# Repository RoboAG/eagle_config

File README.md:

# eagle_config
basics for eagle
 + simple example (logic)
 + some handy shortcuts
 + library for robotics club

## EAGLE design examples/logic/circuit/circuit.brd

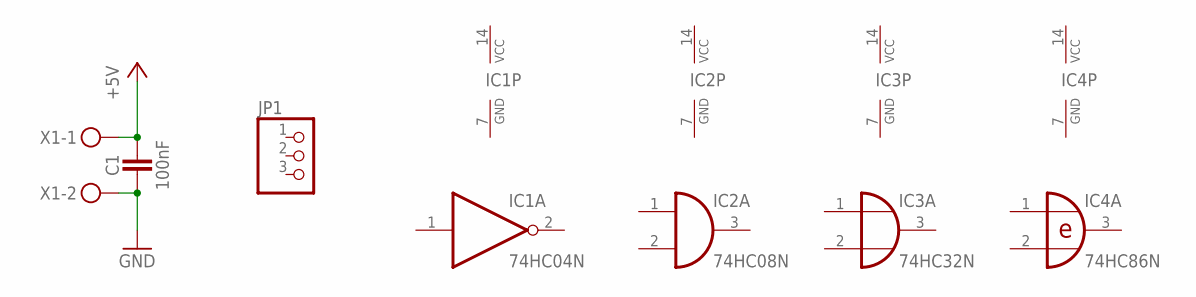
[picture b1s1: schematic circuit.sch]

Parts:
C1: 100nF; C_THT_3
IC1: 74HC04N; DIL14
IC2: 74HC08N; DIL14
IC3: 74HC32N; DIL14
IC4: 74HC86N; DIL14
JP1: PINHD-1X3; 1X03
X1: STECKER_SPG_2

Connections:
+5V: C1.1, X1.1
GND: C1.2, IC1.7 (GND), IC2.7 (GND), IC3.7 (GND), IC4.7 (GND), X1.2
VCC: IC1.14 (VCC), IC2.14 (VCC), IC3.14 (VCC), IC4.14 (VCC)

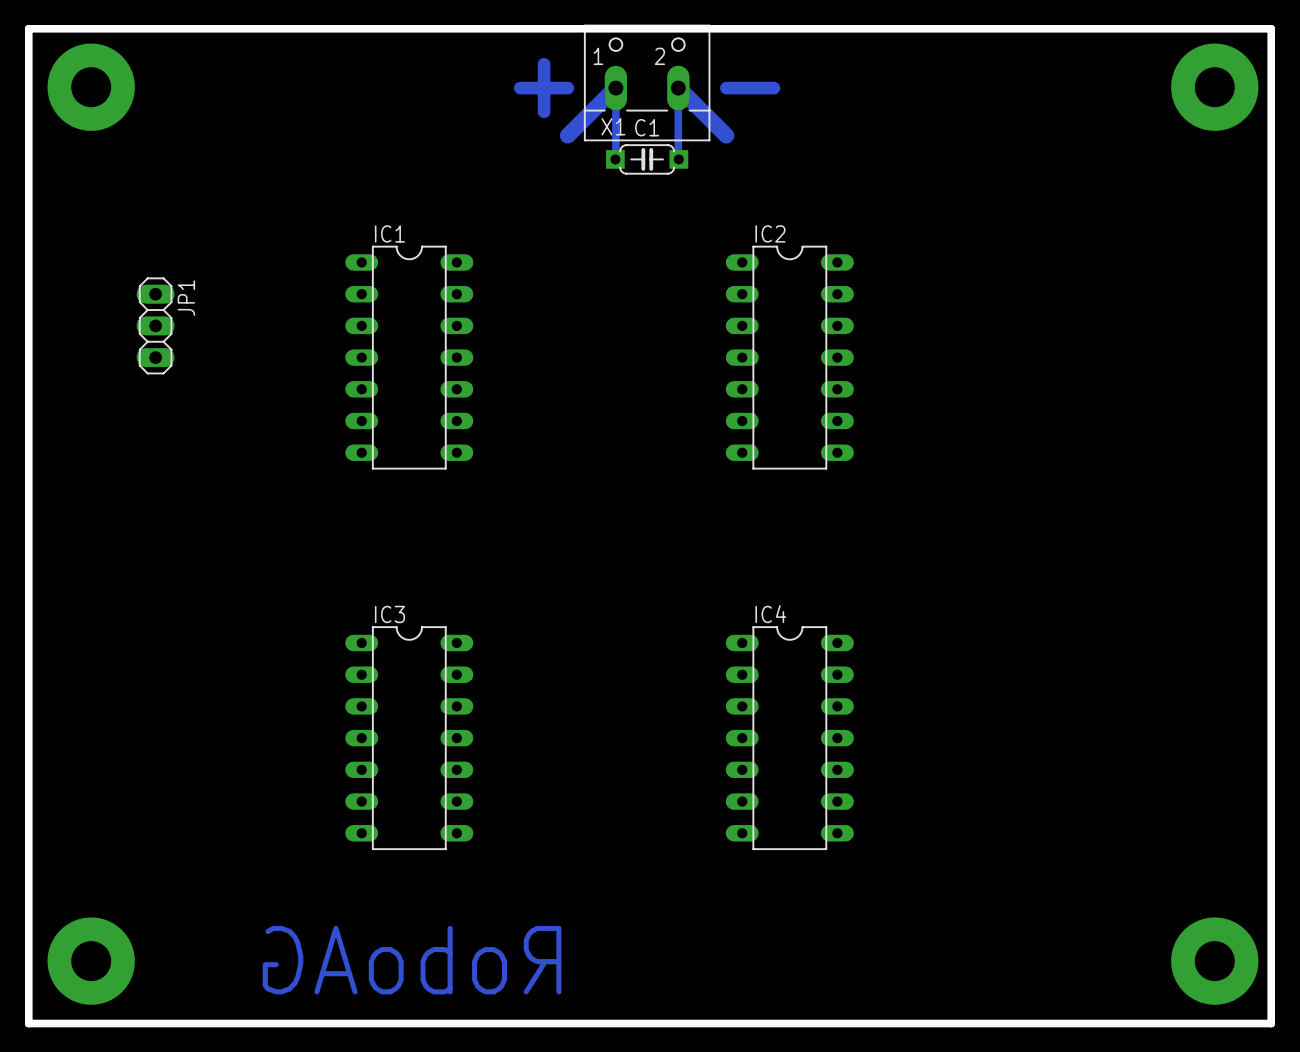
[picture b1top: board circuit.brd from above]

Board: 2 copper layers, 99.5 x 79.7 mm, 7 parts (0 on the bottom side), 3 nets.

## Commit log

2018-01-10 added ISP-Connector
2018-01-24 bugfixed smd-led (removed solder resist)
